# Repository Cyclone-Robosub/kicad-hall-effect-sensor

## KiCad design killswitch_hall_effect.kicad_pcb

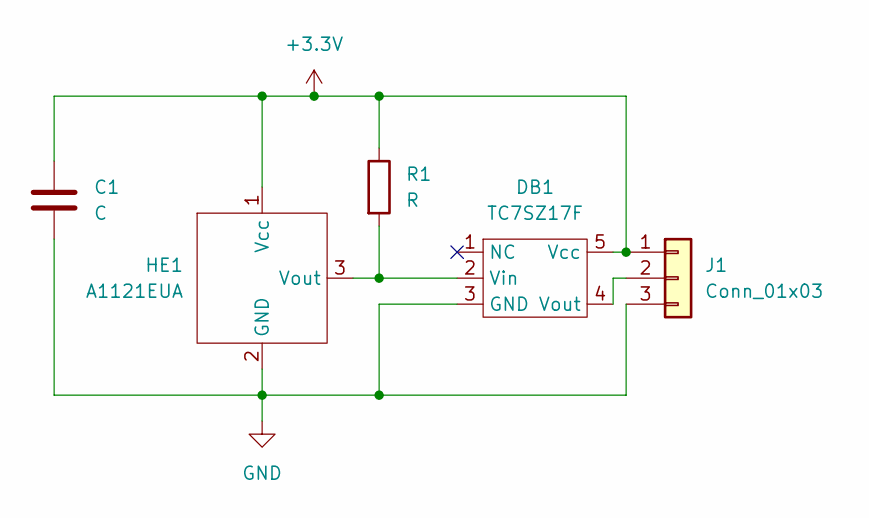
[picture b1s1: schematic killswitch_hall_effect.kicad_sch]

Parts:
C1: C; C_0805_2012Metric
DB1: TC7SZ17F
HE1: A1121EUA; A1211
J1: Conn_01x03; JST_PH_B3B-PH-K_1x03_P2.00mm_Vertical
R1: R; R_0805_2012Metric

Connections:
+3.3V: C1.1, DB1.5 (Vcc), HE1.1 (Vcc), J1.1, R1.1
GND: C1.2, DB1.3 (GND), HE1.2 (GND), J1.3
unnamed: DB1.2 (Vin), HE1.3 (Vout), R1.2
unnamed: DB1.4 (Vout), J1.2

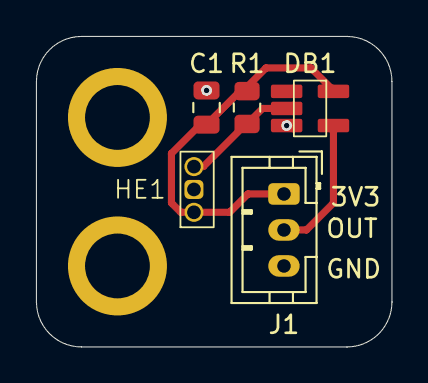
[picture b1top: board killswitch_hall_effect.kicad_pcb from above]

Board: 2 copper layers, 19.8 x 17.2 mm, 5 parts (0 on the bottom side), 4 nets.
